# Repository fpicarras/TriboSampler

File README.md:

# Portable Sampler for Textile Triboelectric Nano-Generators (TENGs) Wearable Sensor System

## Overview

Textile triboelectric nano-generators (TENGs) have emerged as a promising solution for wearable self-powered sensing technology. These flexible TENGs exhibit stable output performance under strong deformation and can be utilized as wearable sensors to monitor biomechanical movements. In this internship project, we focused on the conceptualization of a small, portable electronic device capable of harnessing signals produced by TENGs as sensors and processing the acquired data.

## Objectives

The primary goal of this internship was to explore the potential of TENGs as wearable sensors and to design a system that efficiently captures and transmits the biomechanical movement data.

## Challenges and Solutions

Despite the initial aim of achieving self-sustainability for the electronic device using TENGs, practical limitations were encountered. As a result, we decided to design a low-power and low-profile system powered by two single coin batteries. This system is capable of sampling the sensor data and transmitting it to another device with higher processing capabilities, allowing for more efficient real-time data management.

## System Design

The designed system consists of:
- **Textile Triboelectric Nano-Generators (TENGs):** Serving as wearable sensors to capture biomechanical movement data.
- **Low-Power Circuit:** Powered by two single coin batteries, capable of efficiently sampling the sensor data.
- **Data Transmission:** The system transmits captured data to another device with higher processing capabilities for real-time management.

## Future Considerations

Although the current implementation relies on coin batteries for power, future iterations may explore alternative power sources or energy-efficient improvements to enhance device sustainability.

## Usage

To utilize the system:
1. **Wear the TENGs:** Attach the TENGs to the desired wearable locations.
2. **Power On:** Ensure the low-power circuit is powered by two single coin batteries.
3. **Data Transmission:** The system will transmit the captured data to another device for real-time monitoring.

## Conclusion

This internship project lays the foundation for the development of a wearable sensor system utilizing TENGs for biomechanical movement monitoring. While the goal of achieving complete self-sustainability remains a future consideration, the current design provides a practical and efficient solution for real-time data management in everyday and medical environments.

**Note:** This README serves as a high-level overview. Refer to the project documentation for detailed technical information and instructions.

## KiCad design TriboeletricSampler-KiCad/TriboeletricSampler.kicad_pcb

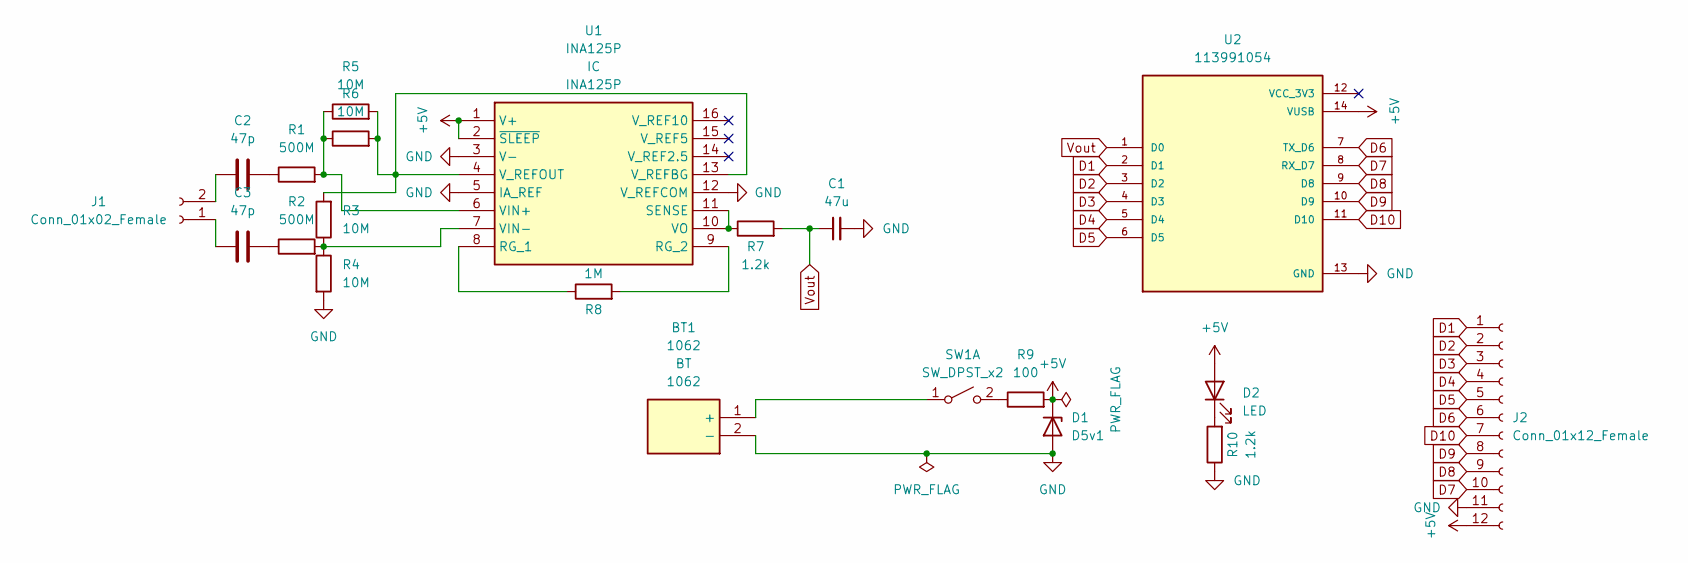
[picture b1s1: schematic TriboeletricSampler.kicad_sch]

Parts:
BT1: 1062; Mouser Part Number 534-1062
C1: 47u; CP_Elec_5x5.4
C2, C3: 47p; CP_EIA-3216-10_Kemet-I
D1: D5v1; D_SOT-23_ANK
D2: LED; LED_1206_3216Metric
J1: Conn_01x02_Female; PinHeader_1x02_P2.54mm_Vertical
J2: Conn_01x12_Female; PinSocket_1x12_P2.54mm_Vertical
R1, R2: 500M; R_0805_2012Metric
R3, R4, R5, R6: 10M; R_1206_3216Metric
R7, R10: 1.2k; R_1206_3216Metric
R8: 1M; R_1206_3216Metric
R9: 100; R_1206_3216Metric
SW1: SW_DPST_x2; SW_DIP_SPSTx01_Slide_Omron_A6S-110x_W8.9mm_P2.54mm
U1: INA125P; DIP794W53P254L1930H508Q16N; Mouser Part Number 595-INA125P
U2: 113991054; MODULE_113991054; PARTREV 23/05/2022

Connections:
+5V: D1.1 (K), D2.2 (A), J2.12, R9.2, U1.1 (V+), U1.2 (~SLEEP), U2.14 (VUSB)
D1: J2.1, U2.2 (D1)
D2: J2.2, U2.3 (D2)
D3: J2.3, U2.4 (D3)
D4: J2.4, U2.5 (D4)
D5: J2.5, U2.6 (D5)
D6: J2.6, U2.7 (TX_D6)
D7: J2.10, U2.8 (RX_D7)
D8: J2.9, U2.9 (D8)
D9: J2.8, U2.10 (D9)
D10: J2.7, U2.11 (D10)
GND: BT1.2 (-), C1.2, D1.2 (A), J2.11, R4.2, R10.1, U1.3 (V-), U1.5 (IA_REF), U1.12 (V_REFCOM), U2.13 (GND)
unnamed: BT1.1 (+), SW1.1 (A)
unnamed: D2.1 (K), R10.2
unnamed: C3.1, J1.1
unnamed: C2.1, J1.2
unnamed: C2.2, R1.1
unnamed: R1.2, R5.1, R6.1, U1.6 (VIN+)
unnamed: C3.2, R2.1
unnamed: R2.2, R3.1, R4.1, U1.7 (VIN-)
unnamed: R3.2, R5.2, R6.2, U1.4 (V_REFOUT), U1.13 (V_REFBG)
unnamed: R7.1, U1.10 (VO), U1.11 (SENSE)
unnamed: R8.1, U1.8 (RG_1)
unnamed: R8.2, U1.9 (RG_2)
unnamed: R9.1, SW1.2 (B)
Vout: C1.1, R7.2, U2.1 (D0)

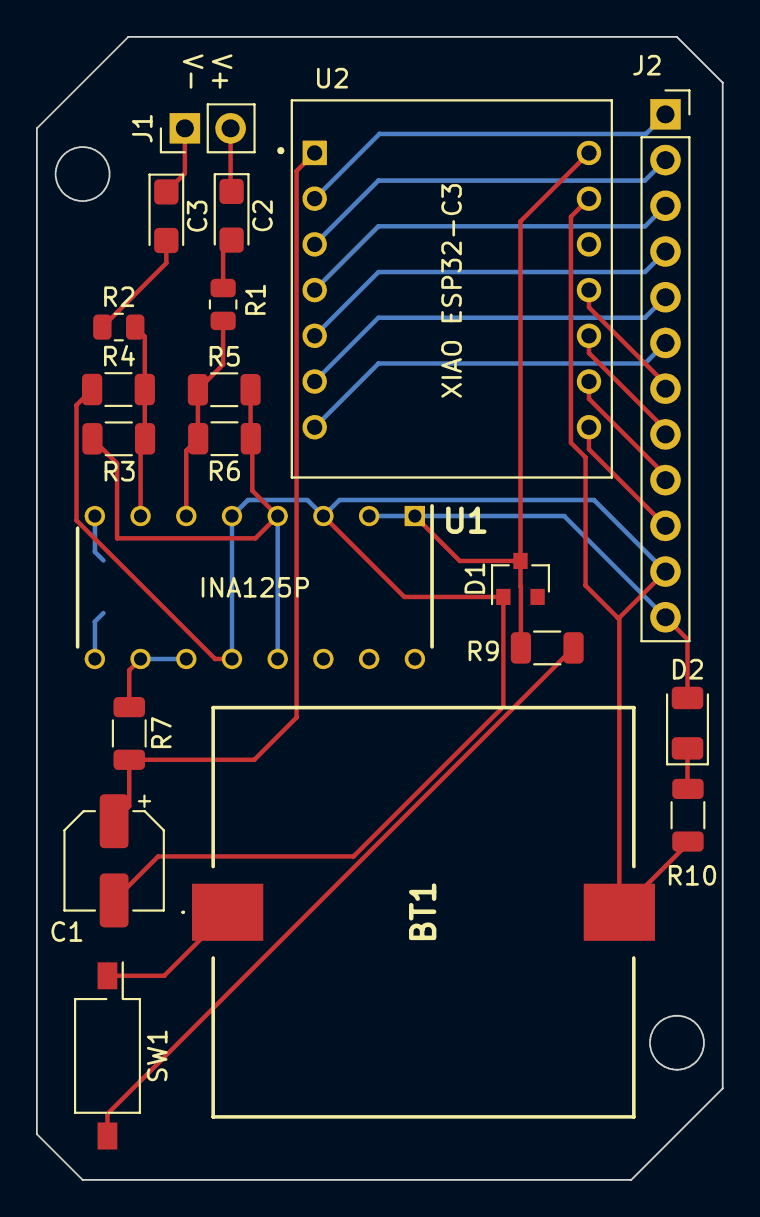
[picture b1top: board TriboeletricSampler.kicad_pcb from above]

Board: 2 copper layers, 38.1 x 63.5 mm, 21 parts (1 on the bottom side), 26 nets.

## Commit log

2023-12-03 Added KiCad files and Sender Code
2023-12-03 Project explanatory pdf and KiCad resources
2023-12-03 User-side Reciever
2023-12-03 Small README.md title change
